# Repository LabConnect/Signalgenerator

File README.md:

LabConnect - DDS-Signalgenerator
================================

In diesem Repository werden die Schaltpläne und Layouts für den LabConnect Signalgenerator zu finden sein.

Was ist geplant?
----------------
* 1Hz bis c.a. 12.5MHz Ausgangsfrequenz in der kleinen Version
* 1Hz bis c.a. 25MHz Ausgangsfrequenz in der großen Version
* Sinus-, Dreieck- und Rechteckförmige Ausgangssignale in der kleinen Version
* Sinusförmiges Ausgangssignal in der großen Version
* Indentifikations LED
* Mikro USB Buchse
* SMA oder SMB Stecker als Signalausgang
* Bauliche Trennung von analoger und digitaler Masse

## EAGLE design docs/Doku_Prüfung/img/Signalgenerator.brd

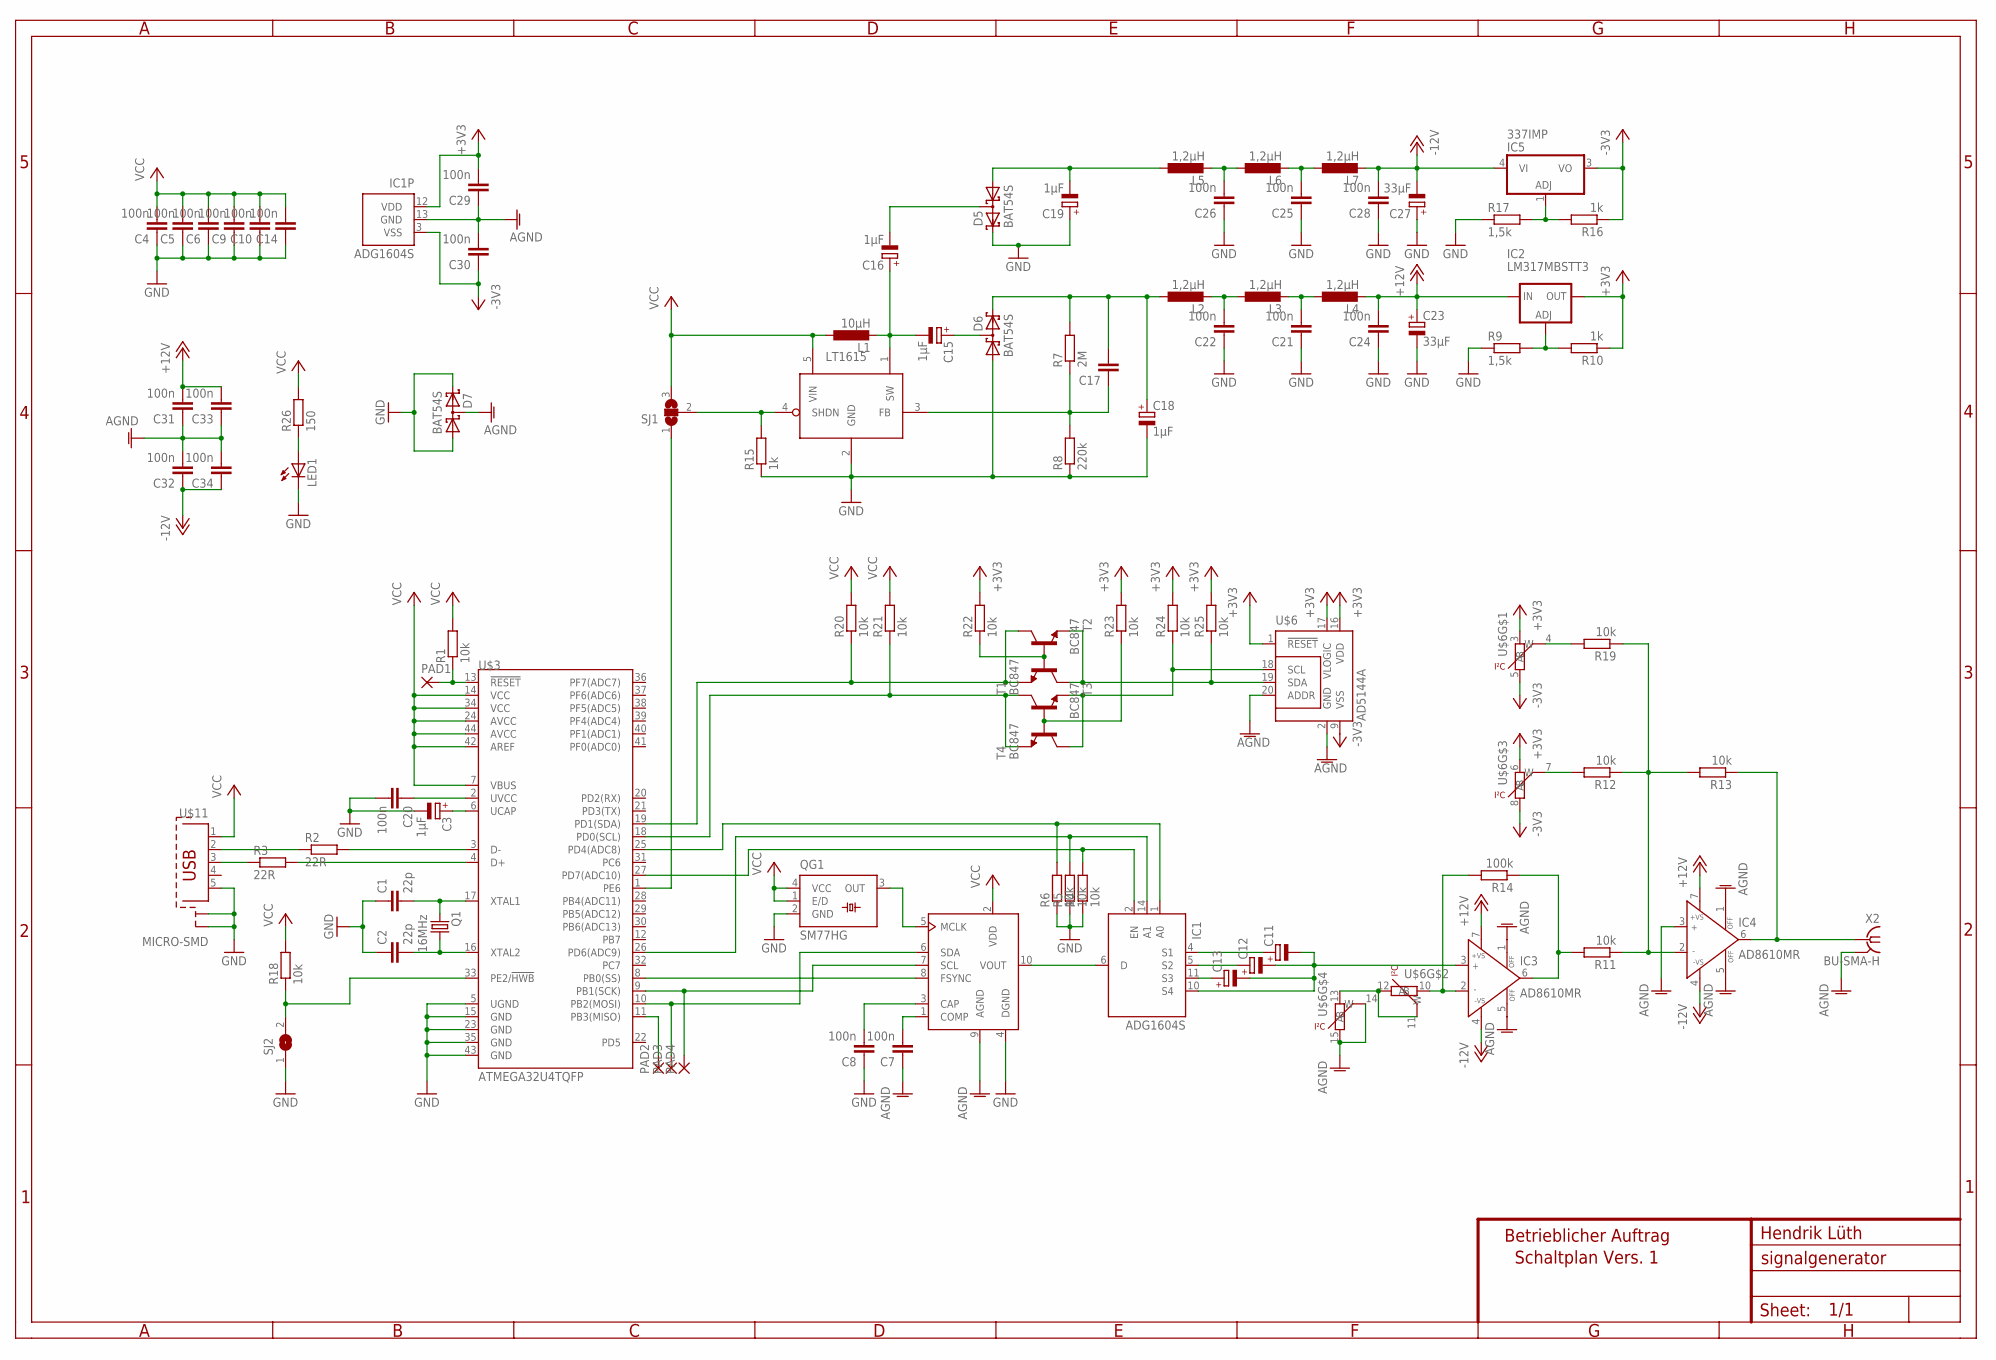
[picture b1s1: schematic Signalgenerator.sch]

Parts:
C1, C2: 22p; C0603
C3, C15, C16, C18, C19: 1µF; SMC_A
C4, C5, C6, C7, C8, C9, C10, C14, C20, C21, C22, C24, C25, C26, C28, C29, C30, C31, C32, C33, C34: 100n; C0603
C11, C12, C13: CPOL-EUSMCB; SMC_B
C17: C-EUC0603; C0603
C23, C27: 33µF; SMC_B
D5, D6, D7: BAT54S; SOT23
IC1: ADG1604S; TSSOP14
IC2: LM317MBSTT3; SOT223
IC3, IC4: AD8610MR; MSOP08
IC5: 337IMP; SOT223
L1: 10µH; L3015
L2, L3, L4, L5, L6, L7: 1,2µH; R0805
LED1: LEDCHIP-LED0603; CHIP-LED0603
PAD1, PAD2, PAD3, PAD4: WIREPADSMD1,27-254; SMD1,27-2,54
Q1: 16MHz; SM77H
QG1: SM77HG; SM77H-G
R1, R4, R5, R6, R11, R12, R13, R18, R19, R20, R21, R22, R23, R24, R25: 10k; R0603
R2, R3: 22R; R0603
R7: 2M; R0603
R8: 220k; R0603
R9, R17: 1,5k; R0603
R10, R15, R16: 1k; R0603
R14: 100k; R0603
R26: 150; R0603
SJ1: SJ2W; SJ_2
SJ2: SJ
T1, T2, T3, T4: BC847; SOT23
U$1: AD9833-SMD; MSOP10
U$2: LT1615; SOT23-5
U$3: ATMEGA32U4TQFP; SPARKFUN-DIGITALIC_TQFP44
U$6: AD5144A; TSSOP20
U$10: A3-LOC; A3L-LOC
U$11: MICRO-SMD; MIKRO
X2: BU-SMA-H

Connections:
+3V3: C29.2, IC1.12 (VDD), IC2.4 (OUT), R10.1, R22.2, R23.2, R24.2, R25.2, U$6.1 (!RESET), U$6.3 (A), U$6.6 (A), U$6.16 (VDD), U$6.17 (VLOGIC)
+12V: C23.+, C24.2, C31.2, C33.2, IC2.3 (IN), IC3.7 (+VS), IC4.7 (+VS), L4.2
-3V3: C30.1, IC1.3 (VSS), IC5.3 (VO), R16.1, U$6.5 (B), U$6.8 (B), U$6.9 (VSS)
-12V: C27.-, C28.2, C32.1, C34.1, IC3.4 (-VS), IC4.4 (-VS), IC5.4 (VI), L7.2
AGND: C7.1, C29.1, C30.2, C31.1, C32.2, C33.1, C34.2, D7.3 (C1A2), IC1.13 (GND), IC3.1 (OFF), IC3.5 (OFF), IC4.1 (OFF), IC4.3 (IN+), IC4.5 (OFF), U$1.9 (AGND), U$6.2 (GND), U$6.14 (W), U$6.15 (B), U$6.20 (ADDR), X2.2, X2.3 (2), X2.4 (2), X2.5 (2)
GND: C1.1, C2.1, C3.-, C4.1, C5.1, C6.1, C8.1, C9.1, C10.1, C14.1, C18.-, C19.+, C20.2, C21.1, C22.1, C23.-, C24.1, C25.1, C26.1, C27.+, C28.1, D5.2 (C2), D6.1 (A1), D7.1 (A1), D7.2 (C2), LED1.C, QG1.2 (GND), R4.1, R5.1, R6.1, R8.1, R9.1, R15.1, R17.1, SJ2.1, U$1.4 (DGND), U$2.2 (GND), U$3.5 (UGND), U$3.15 (GND), U$3.23 (GND), U$3.35 (GND), U$3.43 (GND), U$11.5, U$11.G1 (S1), U$11.G2 (S1), U$11.G3 (S2), U$11.G4 (S2)
unnamed: C2.2, Q1.1, U$3.16 (XTAL2)
unnamed: C1.2, Q1.3 (2), U$3.17 (XTAL1)
unnamed: C15.+, D6.3 (C1A2)
unnamed: PAD3.1, U$1.6 (SDA), U$3.10 (PB2(MOSI))
unnamed: R2.2, U$3.3 (D-)
unnamed: R3.2, U$3.4 (D+)
unnamed: R18.1, SJ2.2, U$3.33 (PE2/!HWB)
unnamed: PAD1.1, R1.1, U$3.13 (!RESET)
unnamed: PAD4.1, U$1.7 (SCL), U$3.9 (PB1(SCK))
unnamed: U$1.8 (FSYNC), U$3.8 (PB0(SS))
unnamed: C8.2, U$1.3 (CAP)
unnamed: C7.2, U$1.1 (COMP)
unnamed: R3.1, U$11.3
unnamed: R2.1, U$11.2
unnamed: QG1.3 (OUT), U$1.5 (MCLK)
unnamed: IC1.6 (D), U$1.10 (VOUT)
unnamed: C13.+, IC1.11 (S3)
unnamed: C12.+, IC1.5 (S2)
unnamed: C11.+, IC1.4 (S1)
unnamed: C11.-, C12.-, C13.-, IC1.10 (S4), IC3.3 (IN+)
unnamed: IC1.2 (EN), R4.2, U$3.27 (PD7(ADC10))
unnamed: IC1.14 (A1), R5.2, U$3.26 (PD6(ADC9))
unnamed: IC1.1 (A0), R6.2, U$3.25 (PD4(ADC8))
unnamed: C16.-, D5.3 (C1A2)
unnamed: C15.-, C16.+, L1.P$2 (2), U$2.1 (SW)
unnamed: C22.2, L2.2, L3.1
unnamed: C17.1, R7.1, R8.2, U$2.3 (FB)
unnamed: C21.2, L3.2, L4.1
unnamed: C17.2, C18.+, D6.2 (C2), L2.1, R7.2
unnamed: IC2.1 (ADJ), R9.2, R10.2
unnamed: C19.-, D5.1 (A1), L5.1
unnamed: IC4.2 (IN-), R11.1, R12.1, R13.2, R19.1
unnamed: R19.2, U$6.4 (W)
unnamed: IC3.2 (IN-), R14.2, U$6.10 (A)
unnamed: IC3.6 (OUT), R11.2, R14.1
unnamed: IC4.6 (OUT), R13.1, X2.1
unnamed: C26.2, L5.2, L6.1
unnamed: C25.2, L6.2, L7.1
unnamed: SJ1.1, U$3.1 (PE6)
unnamed: R15.2, SJ1.2, U$2.4 (SHDN)
unnamed: IC5.1 (ADJ), R16.2, R17.2
unnamed: R21.1, T3.2 (E), T4.3 (C), U$3.18 (PD0(SCL))
unnamed: R20.1, T1.3 (C), T2.2 (E), U$3.19 (PD1(SDA))
unnamed: U$6.11 (W), U$6.12 (B), U$6.13 (A)
unnamed: R12.2, U$6.7 (W)
unnamed: R22.1, T1.1 (B), T2.1 (B)
unnamed: R23.1, T3.1 (B), T4.1 (B)
unnamed: R24.1, T3.3 (C), T4.2 (E), U$6.18 (SCL)
unnamed: R25.1, T1.2 (E), T2.3 (C), U$6.19 (SDA)
unnamed: PAD2.1, U$3.11 (PB3(MISO))
unnamed: LED1.A, R26.1
unnamed: C3.+, U$3.6 (UCAP)
unnamed: C20.1, U$3.2 (UVCC)
VCC: C4.2, C5.2, C6.2, C9.2, C10.2, C14.2, L1.P$1 (1), QG1.1 (E/D), QG1.4 (VCC), R1.2, R18.2, R20.2, R21.2, R26.2, SJ1.3, U$1.2 (VDD), U$2.5 (VIN), U$3.7 (VBUS), U$3.14 (VCC), U$3.24 (AVCC), U$3.34 (VCC), U$3.42 (AREF), U$3.44 (AVCC), U$11.1

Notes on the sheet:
Hendrik Lüth
Betrieblicher Auftrag
Schaltplan Vers. 1

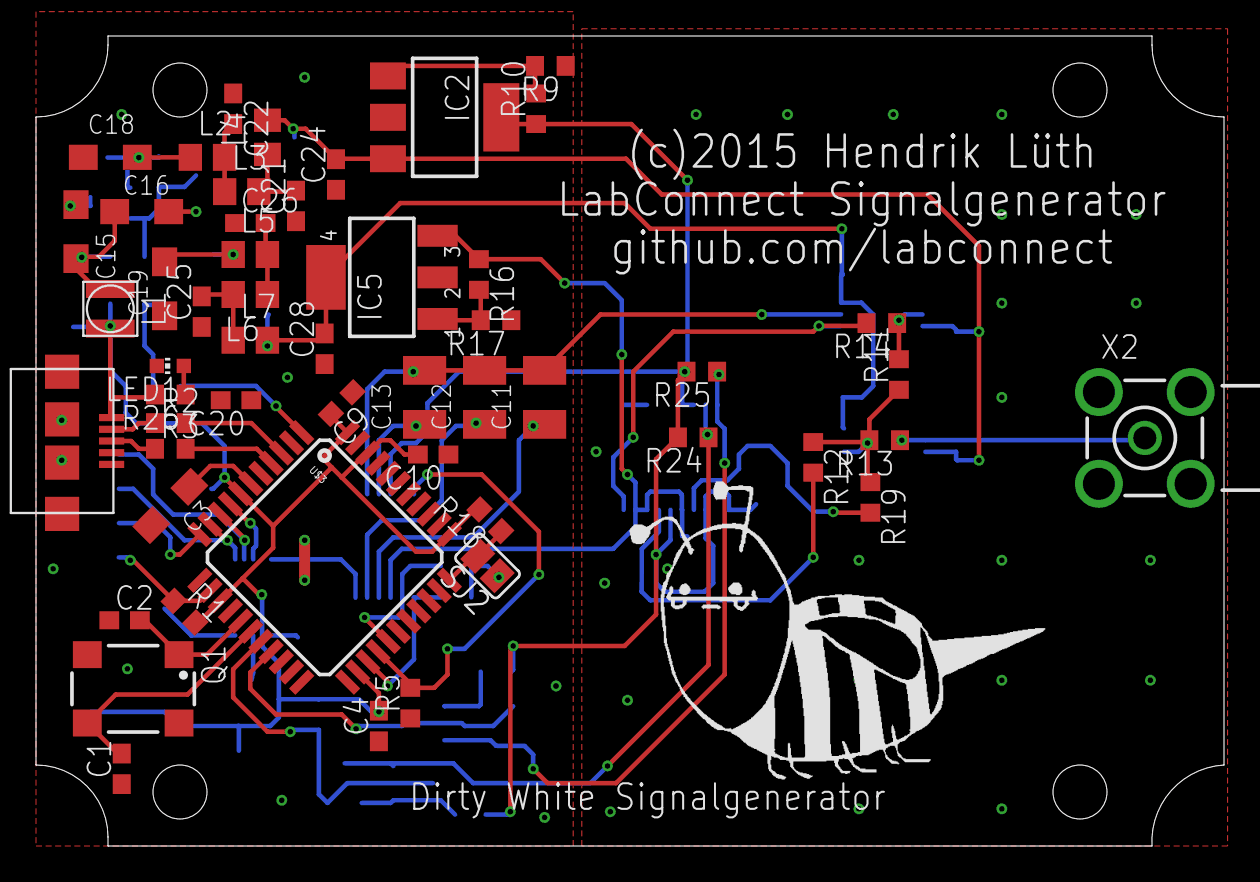
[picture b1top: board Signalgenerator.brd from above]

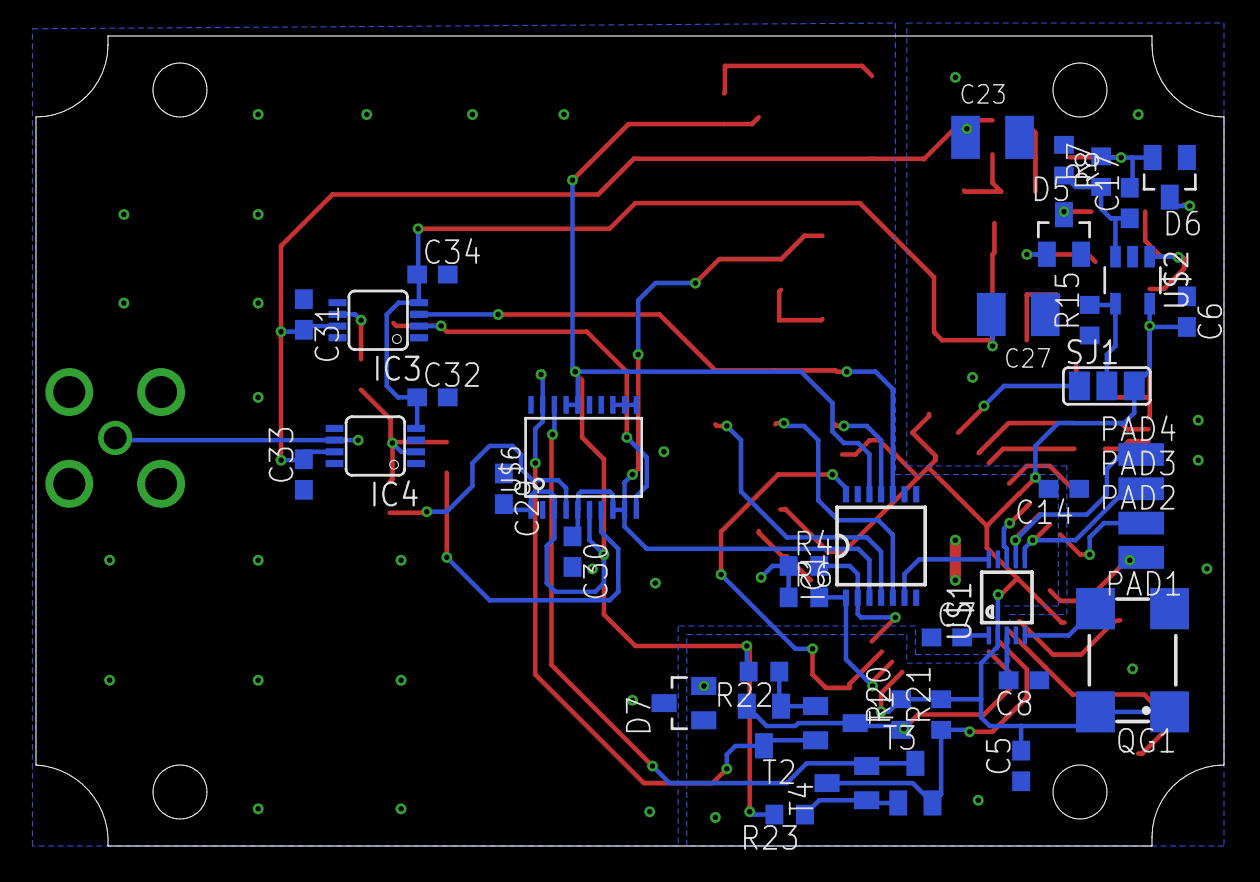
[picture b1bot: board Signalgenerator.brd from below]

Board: 2 copper layers, 66.0 x 45.0 mm, 96 parts (42 on the bottom side), 60 nets.

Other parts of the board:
U$12: BIENE

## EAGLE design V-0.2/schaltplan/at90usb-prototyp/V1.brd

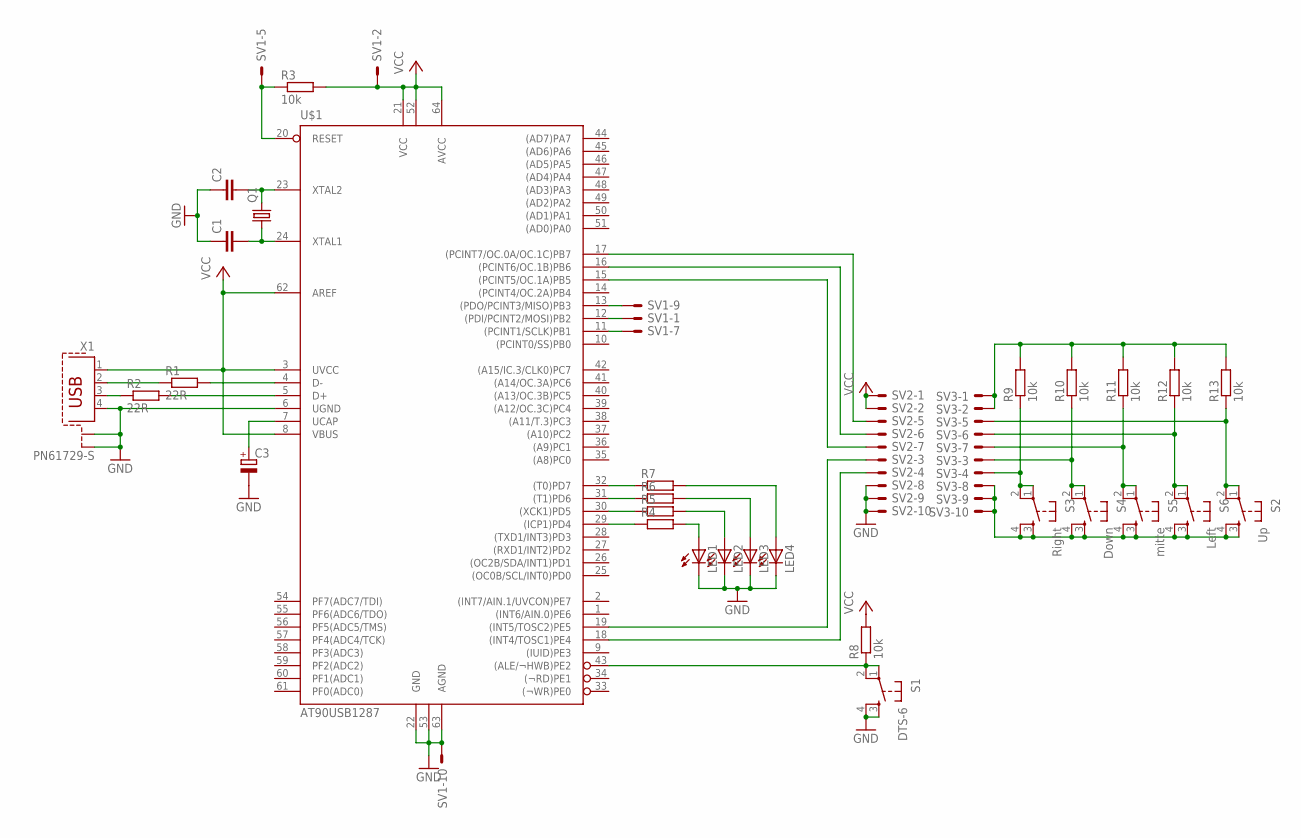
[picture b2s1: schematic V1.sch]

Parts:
C1, C2: C-EUC1206K; C1206K
C3: CPOL-EUE2-5; E2-5
LED1, LED2, LED3, LED4: LED3MM
Q1: CRYSTALSM77H; SM77H
R1, R2: 22R; M1206
R3: 10k; 0207/10
R4, R5, R6, R7: R-EU_0207/10; 0207/10
R8, R9, R10, R11, R12, R13: 10k; M1206
S1: DTS-6
S2: Up; DTS-6
S3: Right; DTS-6
S4: Down; DTS-6
S5: mitte; DTS-6
S6: Left; DTS-6
SV1, SV2, SV3: ML10E; ML10
U$1: AT90USB1287; TQFP64
X1: PN61729-S

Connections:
GND: C1.1, C2.1, C3.-, LED1.K (C), LED2.K (C), LED3.K (C), LED4.K (C), S1.3, S1.4, SV1.10, SV2.8, SV2.9, SV2.10, U$1.6 (UGND), U$1.22 (GND), U$1.53 (GND1), U$1.63 (AGND), X1.4, X1.S1, X1.S2
unnamed: R1.2, U$1.4 (D-)
unnamed: R2.2, U$1.5 (D+)
unnamed: R1.1, X1.2
unnamed: R2.1, X1.3
unnamed: C2.2, Q1.3 (2), U$1.23 (XTAL2)
unnamed: C1.2, Q1.1, U$1.24 (XTAL1)
unnamed: R4.1, U$1.29 ((ICP1)PD4)
unnamed: C3.+, U$1.7 (UCAP)
unnamed: R5.1, U$1.30 ((XCK1)PD5)
unnamed: R6.1, U$1.31 ((T1)PD6)
unnamed: R3.1, SV1.5, U$1.20 (RESET)
unnamed: SV1.9, U$1.13 ((PDO/PCINT3/MISO)PB3)
unnamed: SV1.1, U$1.12 ((PDI/PCINT2/MOSI)PB2)
unnamed: SV1.7, U$1.11 ((PCINT1/SCLK)PB1)
unnamed: R7.1, U$1.32 ((T0)PD7)
unnamed: LED1.A, R4.2
unnamed: LED2.A, R5.2
unnamed: LED3.A, R6.2
unnamed: LED4.A, R7.2
unnamed: R8.1, S1.1, S1.2, U$1.43 ((ALE/¬HWB)PE2)
unnamed: R13.1, S2.1, S2.2, SV3.5
unnamed: R12.1, S6.1, S6.2, SV3.6
unnamed: SV2.4, U$1.18 ((INT4/TOSC1)PE4)
unnamed: SV2.3, U$1.19 ((INT5/TOSC2)PE5)
unnamed: SV2.7, U$1.15 ((PCINT5/OC.1A)PB5)
unnamed: SV2.6, U$1.16 ((PCINT6/OC.1B)PB6)
unnamed: SV2.5, U$1.17 ((PCINT7/OC.0A/OC.1C)PB7)
unnamed: R11.1, S5.1, S5.2, SV3.7
unnamed: R10.1, S4.1, S4.2, SV3.3
unnamed: R9.1, S3.1, S3.2, SV3.4
unnamed: S2.3, S2.4, S3.3, S3.4, S4.3, S4.4, S5.3, S5.4, S6.3, S6.4, SV3.8, SV3.9, SV3.10
unnamed: R9.2, R10.2, R11.2, R12.2, R13.2, SV3.1, SV3.2
VCC: R3.2, R8.2, SV1.2, SV2.1, SV2.2, U$1.3 (UVCC), U$1.8 (VBUS), U$1.21 (VCC), U$1.52 (VCC1), U$1.62 (AREF), U$1.64 (AVCC), X1.1

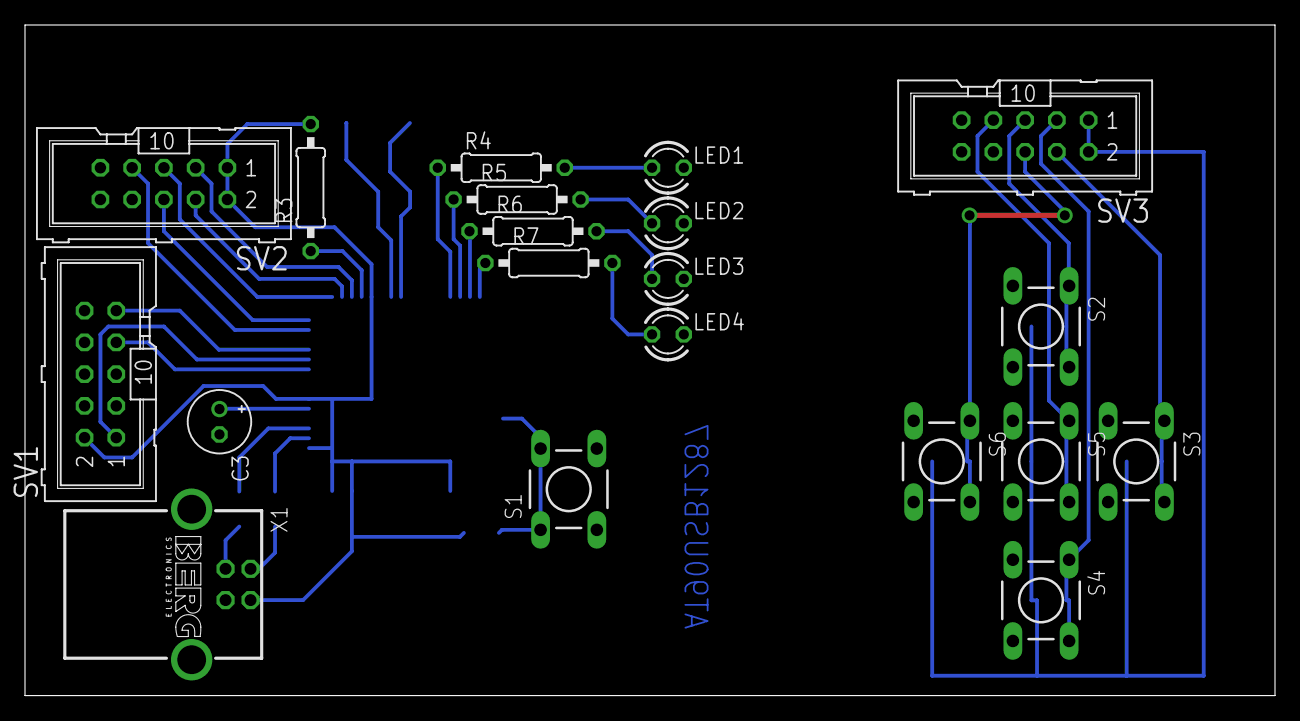
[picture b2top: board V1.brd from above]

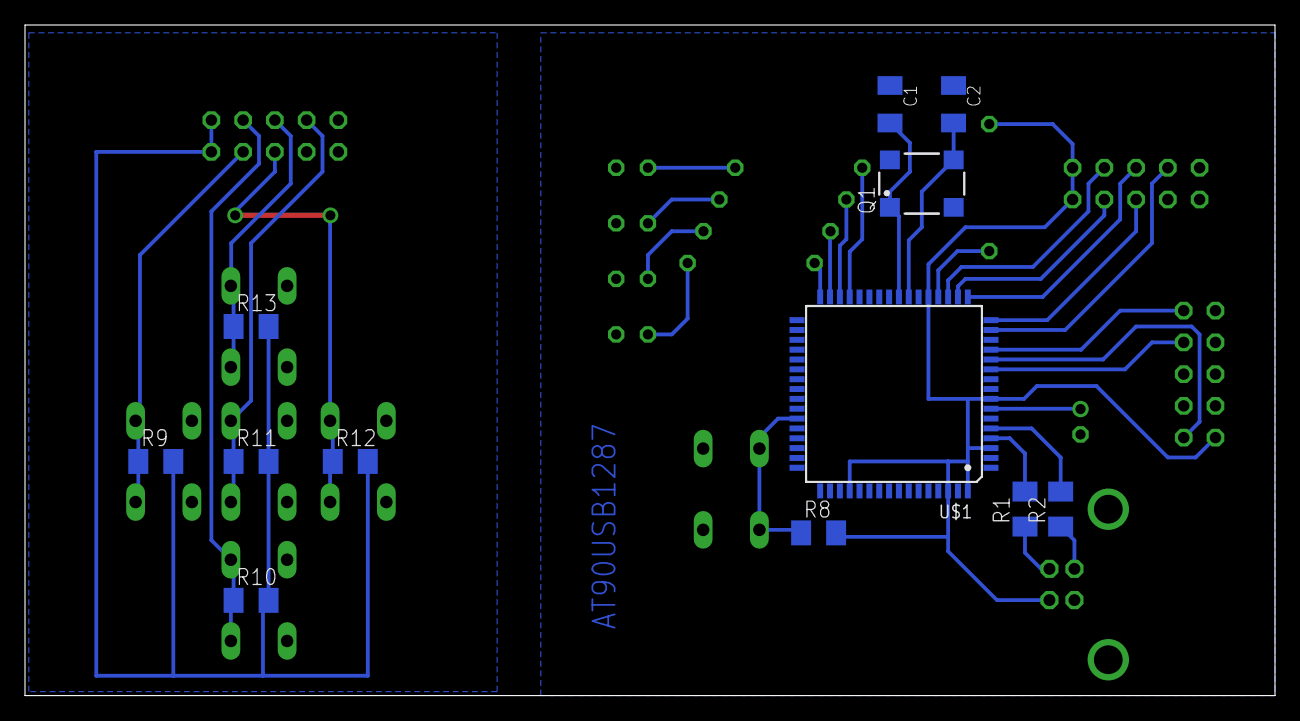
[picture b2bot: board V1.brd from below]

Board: 2 copper layers, 100.0 x 53.6 mm, 32 parts (12 on the bottom side), 34 nets.

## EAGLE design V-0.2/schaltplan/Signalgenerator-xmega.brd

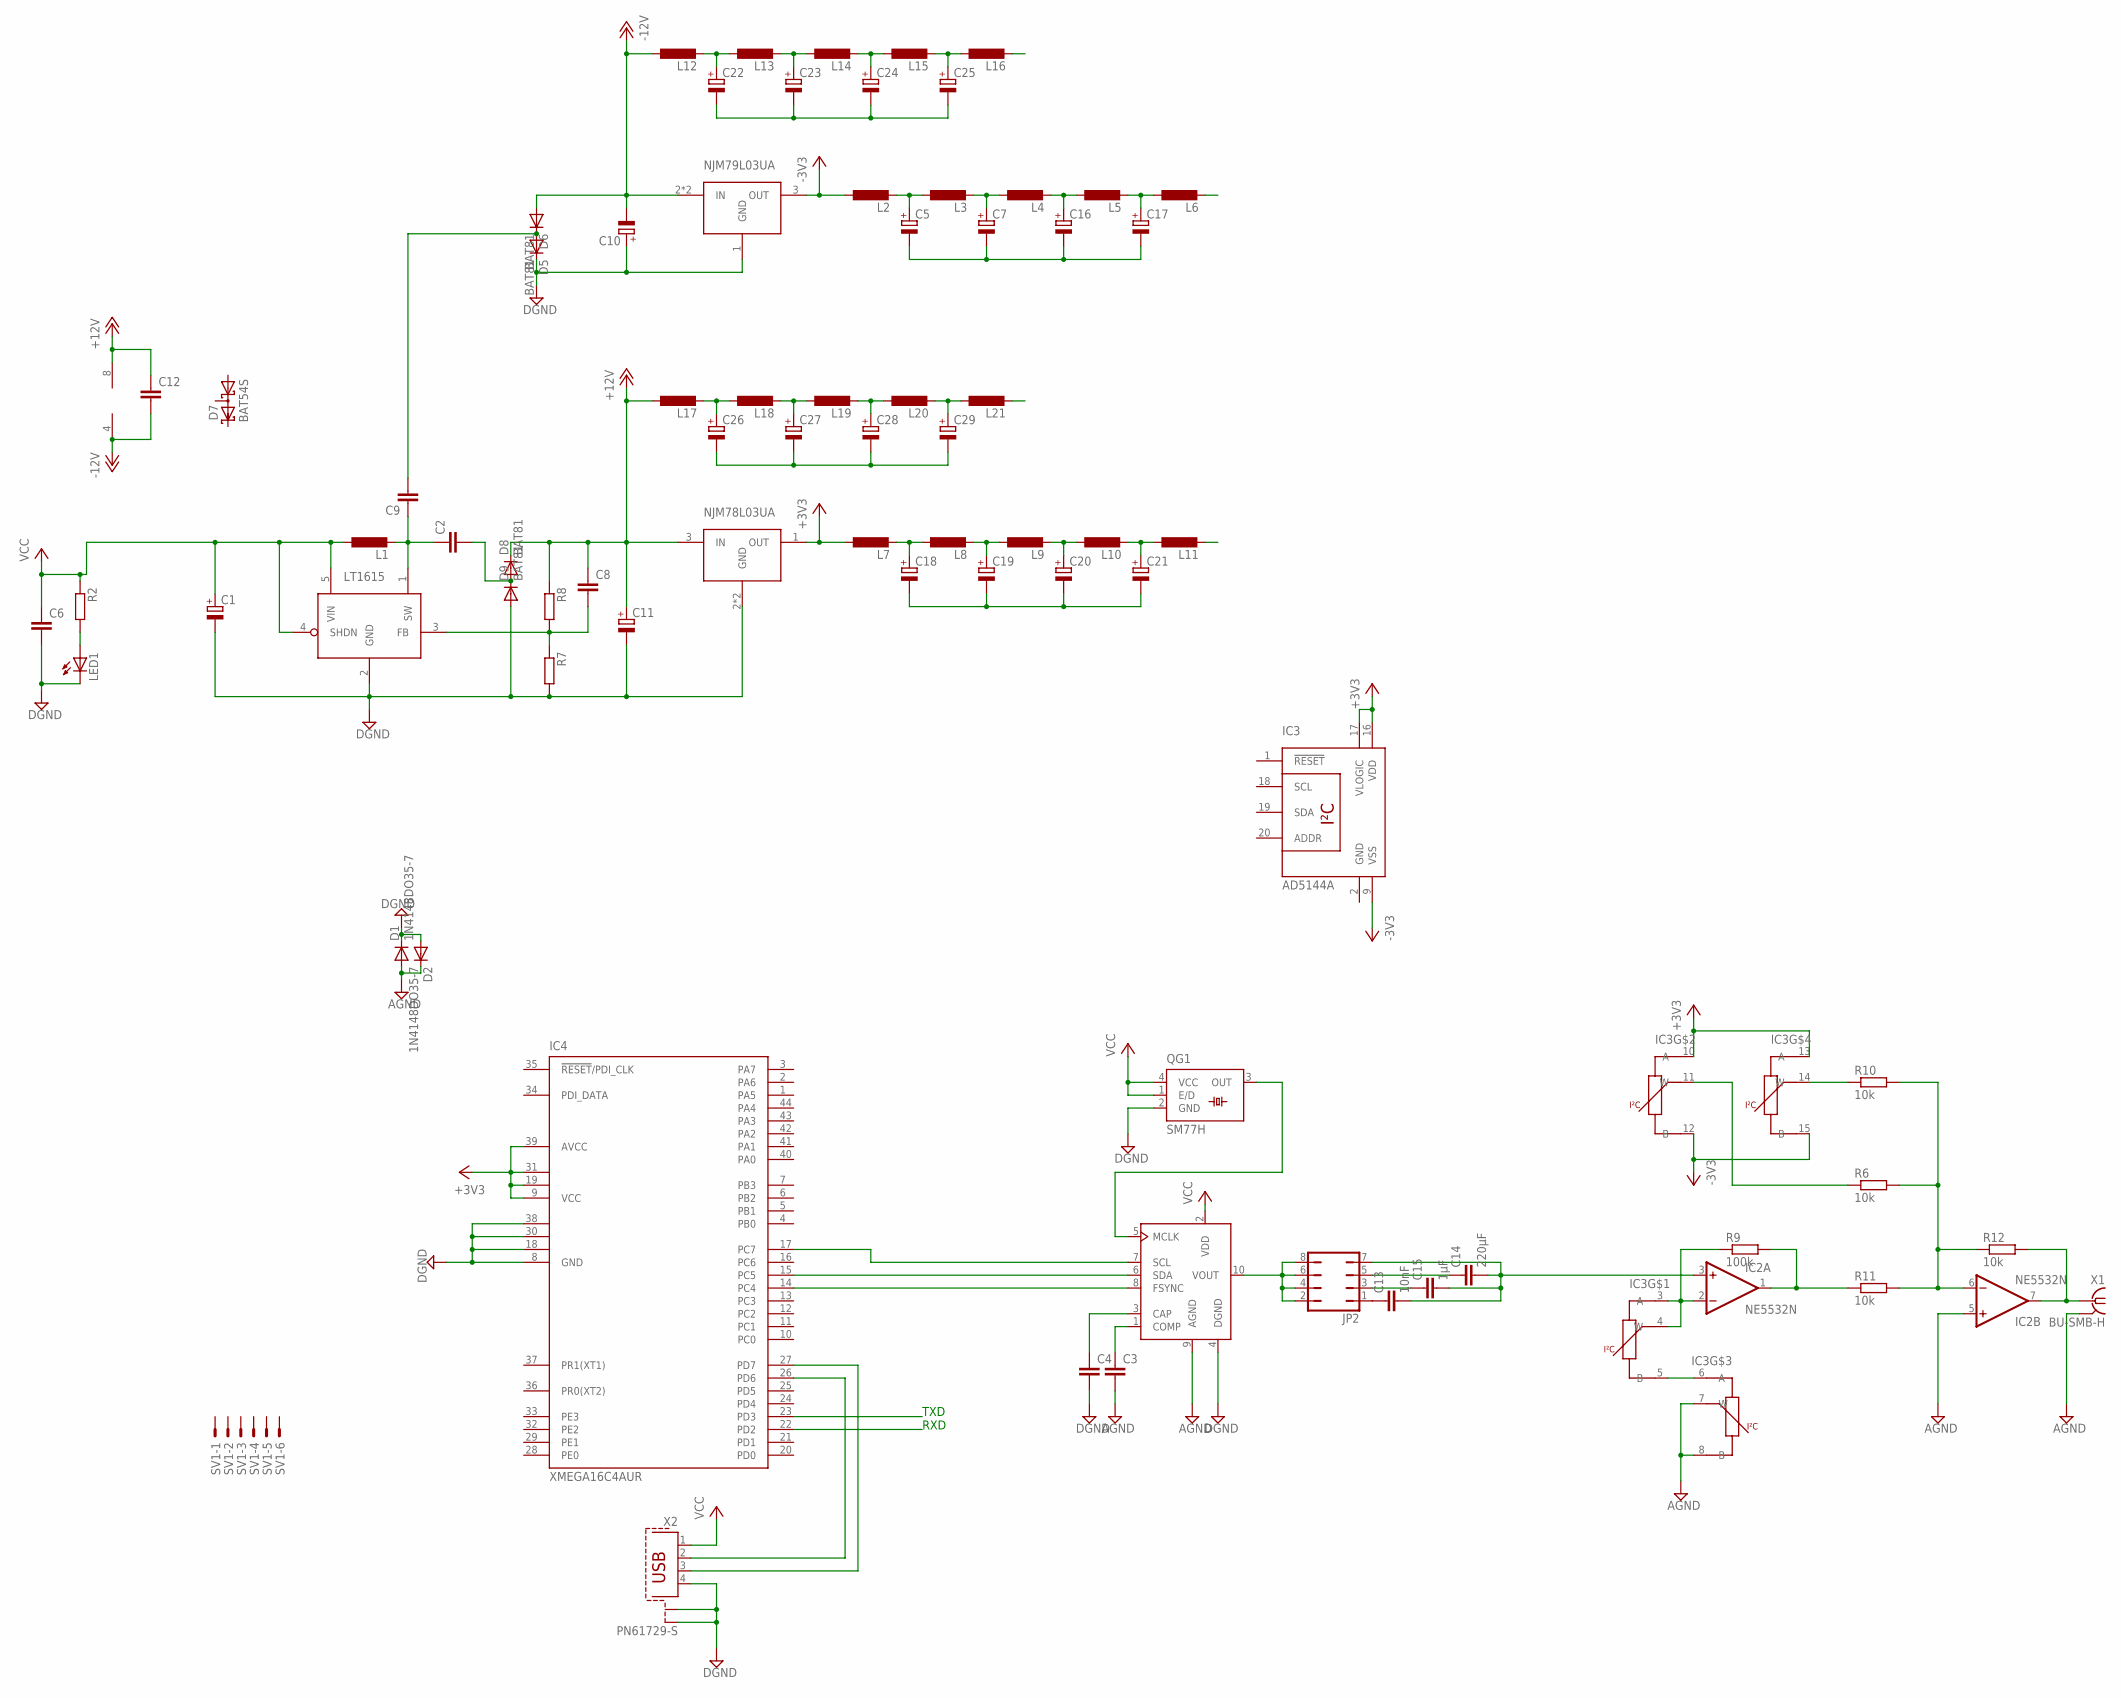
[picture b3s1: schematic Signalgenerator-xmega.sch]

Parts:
C1, C10, C11: CPOL-EUE3.5-8; E3,5-8
C2, C3, C4, C6, C8, C9, C12: C-EU025-024X044; C025-024X044
C5, C7, C16, C17, C18, C19, C20, C21, C22, C23, C24, C25, C26, C27, C28, C29: CPOL-EUE2.5-7; E2,5-7
C13: 10nF; C025-024X044
C14: 220µF; C025-024X044
C15: 1µF; C025-024X044
D1, D2: 1N4148DO35-7; DO35-7
D5, D6, D8, D9: BAT81; DO34-7
D7: BAT54S; SOT23
IC2: NE5532N; DIL08
IC3: AD5144A; TSSOP20
IC4: XMEGA16C4AUR; TQFP44
JP2: JP4Q
L1, L2, L3, L4, L5, L6, L7, L8, L9, L10, L11, L12, L13, L14, L15, L16, L17, L18, L19, L20, L21: L-EU0207/10; 0207/10
LED1: LED5MM
QG1: SM77H
R2, R7, R8: R-EU_0207/10; 0207/10
R6, R10, R11, R12: 10k; 0207/10
R9: 100k; 0207/10
SV1: ML6E; ML6
U$1: AD9833-P; DIL10
U$2: LT1615; SOT23-5
U$3: NJM79L03UA; SOT89
U$4: NJM78L03UA; SOT89
X1: BU-SMB-H
X2: PN61729-S

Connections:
+3V3: IC3.10 (A), IC3.13 (A), IC3.16 (VDD), IC3.17 (VLOGIC), IC4.9 (VCC), IC4.19 (VCC1), IC4.31 (VCC2), IC4.39 (AVCC), L7.1, U$4.1 (OUT)
+12V: C8.1, C11.+, C12.1, D8.C, IC2.8 (V+), L17.1, R8.1, U$4.3 (IN)
-3V3: IC3.9 (VSS), IC3.12 (B), IC3.15 (B), L2.1, U$3.3 (OUT)
-12V: C10.-, C12.2, D6.A, IC2.4 (V-), L12.1, U$3.2 (IN), U$3.2@1 (IN)
AGND: C3.2, D1.A, D2.C, IC2.5 (+IN), IC3.7 (W), IC3.8 (B), U$1.9 (AGND), X1.2, X1.3 (2), X1.4 (2), X1.5 (2)
DGND: C1.-, C4.2, C6.2, C10.+, C11.-, D1.C, D2.A, D5.C, D9.A, IC4.8 (GND), IC4.18 (GND1), IC4.30 (GND2), IC4.38 (GND3), LED1.K (C), QG1.2 (GND), R7.2, U$1.4 (DGND), U$2.2 (GND), U$3.1 (GND), U$4.2 (GND), U$4.2@1 (GND), X2.4, X2.S1, X2.S2
unnamed: IC4.17 (PC7), U$1.7 (SCL)
unnamed: IC4.26 (PD6), X2.2
unnamed: C3.1, U$1.1 (COMP)
unnamed: IC4.15 (PC5), U$1.6 (SDA)
unnamed: IC4.27 (PD7), X2.3
unnamed: IC4.14 (PC4), U$1.8 (FSYNC)
unnamed: C5.-, C7.-, C16.-, C17.-
unnamed: C5.+, L2.2, L3.1
unnamed: C4.1, U$1.3 (CAP)
unnamed: C7.+, L3.2, L4.1
unnamed: QG1.3 (OUT), U$1.5 (MCLK)
unnamed: C16.+, L4.2, L5.1
unnamed: C17.+, L5.2, L6.1
unnamed: LED1.A, R2.2
unnamed: C18.+, L7.2, L8.1
unnamed: C19.+, L8.2, L9.1
unnamed: C8.2, R7.1, R8.2, U$2.3 (FB)
unnamed: JP2.2, JP2.4, JP2.6, JP2.8, U$1.10 (VOUT)
unnamed: C9.2, D5.A, D6.C
unnamed: C2.1, C9.1, L1.2, U$2.1 (SW)
unnamed: C14.1, JP2.5
unnamed: C2.2, D8.A, D9.C
unnamed: C13.1, JP2.1
unnamed: IC2.2 (-IN), IC3.3 (A), IC3.4 (W), R9.1
unnamed: C13.2, C14.2, C15.2, IC2.3 (+IN), JP2.7
unnamed: IC2.1 (OUT), R9.2, R11.1
unnamed: IC2.6 (-IN), R6.2, R10.2, R11.2, R12.1
unnamed: IC2.7 (OUT), R12.2, X1.1
unnamed: C15.1, JP2.3
unnamed: IC3.5 (B), IC3.6 (A)
unnamed: IC3.14 (W), R10.1
unnamed: IC3.11 (W), R6.1
unnamed: C20.+, L9.2, L10.1
unnamed: C21.+, L10.2, L11.1
unnamed: C18.-, C19.-, C20.-, C21.-
unnamed: C22.+, L12.2, L13.1
unnamed: C23.+, L13.2, L14.1
unnamed: C24.+, L14.2, L15.1
unnamed: C25.+, L15.2, L16.1
unnamed: C22.-, C23.-, C24.-, C25.-
unnamed: C26.+, L17.2, L18.1
unnamed: C27.+, L18.2, L19.1
unnamed: C28.+, L19.2, L20.1
unnamed: C29.+, L20.2, L21.1
unnamed: C26.-, C27.-, C28.-, C29.-
VCC: C1.+, C6.1, L1.1, QG1.1 (E/D), QG1.4 (VCC), R2.1, U$1.2 (VDD), U$2.4 (SHDN), U$2.5 (VIN), X2.1

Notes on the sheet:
TXD RXD

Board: 2 copper layers, 78 parts (6 on the bottom side), 52 nets, no tracks yet.

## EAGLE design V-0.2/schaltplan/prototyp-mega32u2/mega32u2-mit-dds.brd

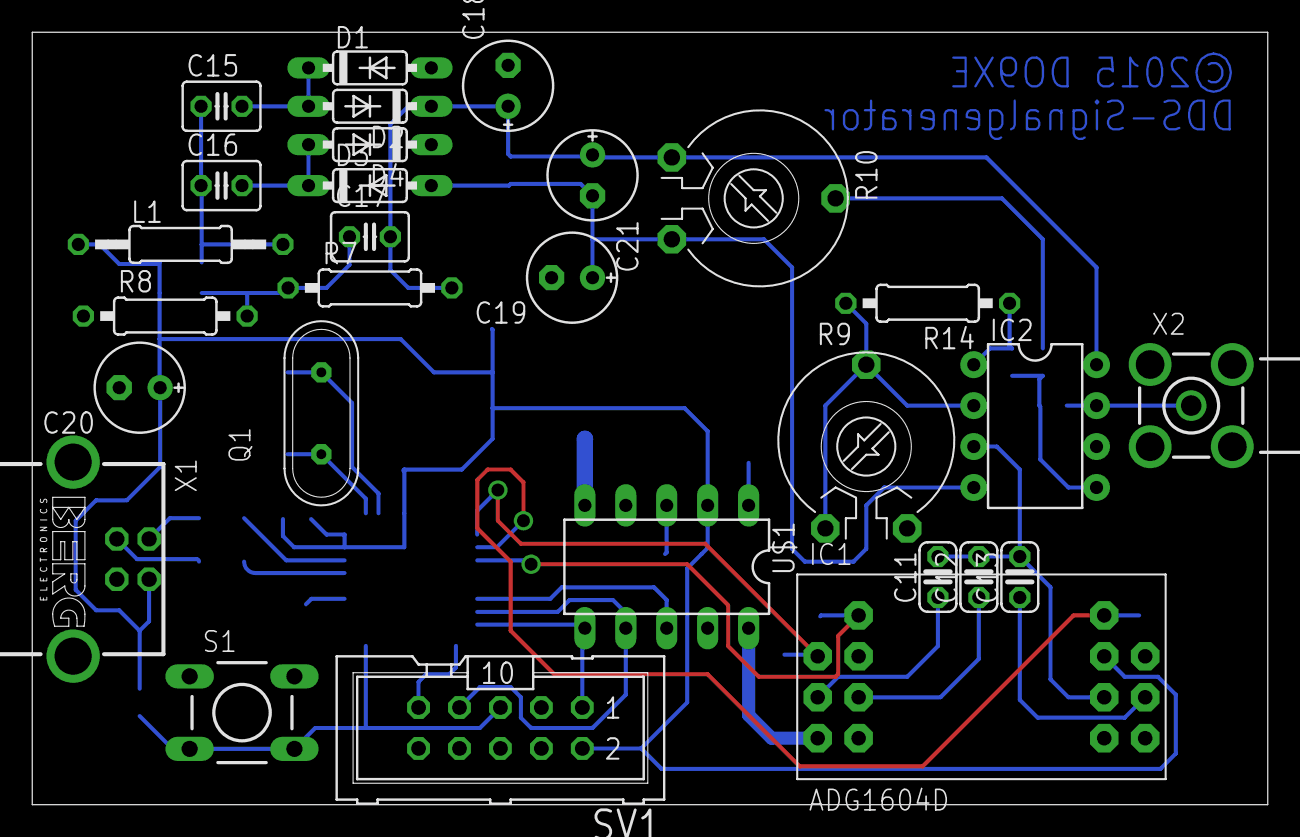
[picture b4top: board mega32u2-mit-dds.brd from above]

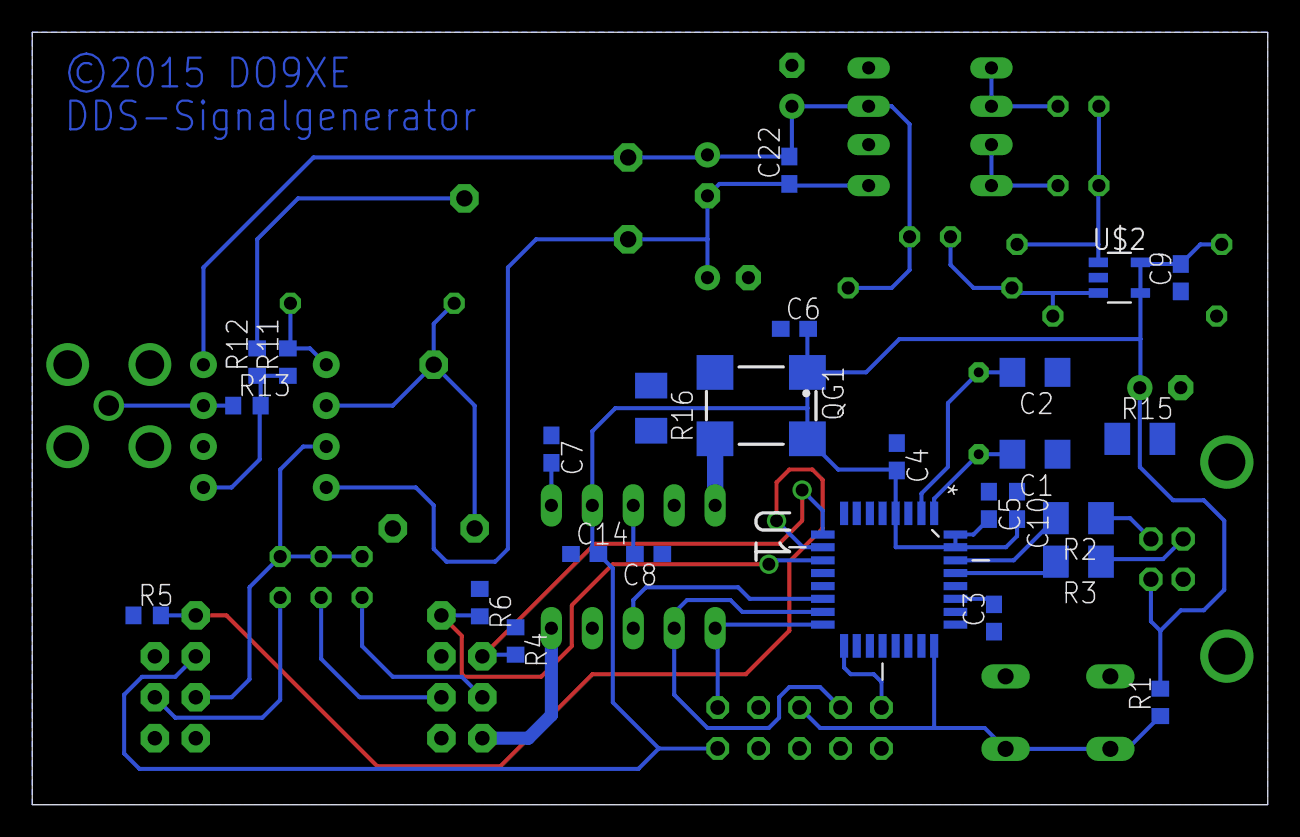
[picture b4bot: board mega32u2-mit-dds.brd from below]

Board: 2 copper layers, 76.7 x 47.9 mm, 54 parts (26 on the bottom side), 36 nets.

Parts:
C1, C2: 22n; C1206
C3, C4, C5, C6, C7, C8, C9, C10, C14, C22: 100n; C0603
C11, C12, C13: C025-024X044
C15, C16, C17: C025-030X050
C18, C19, C20, C21: E2,5-6E
D1, D2, D3, D4: DO35-7
IC1: ADG1604D; DIL2-14
IC2: NE5532N; DIL08
L1: 0207/12
Q1: QS
QG1: SM77HG; SM77H-G
R1, R4, R5, R6, R11, R12, R13: 10k; R0603
R2, R3: 22R; M1206
R7: 2M; 0207/10
R8: 220k; 0207/10
R9: 100k; PT-10
R10: PT-10
R14: 100k; 0207/10
R15: M1206
R16: 0; M1206
S1: DTS-6
SV1: ML10
U1: ATMEGA32U2-AU; QFP80P900X900X120-32N
U$1: AD9833-P; DIL10
U$2: LT1615; SOT23-5
X1: PN61729-S
X2: BU-SMA-H

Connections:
GND: C1.1, C2.1, C3.1, C4.1, C5.1, C6.1, C7.1, C8.1, C9.1, C10.1, C14.1, C18.-, C19.-, C20.-, D1.A, D4.C, IC1.P$3, IC1.P$13, IC2.6, QG1.2, R4.1, R5.1, R6.1, R8.1, R9.2, R15.1, R15.2, R16.1, R16.2, S1.1, S1.2, SV1.10, U1.3, U1.28, U$1.4, U$1.9, U$2.2, X1.4, X1.S1, X1.S2, X2.2, X2.3, X2.4, X2.5
unnamed: C2.2, Q1.2, U1.2
unnamed: C1.2, Q1.1, U1.1
unnamed: SV1.9, U1.17
unnamed: SV1.1, U1.16, U$1.6
unnamed: R2.2, U1.30
unnamed: R3.2, U1.29
unnamed: C3.2, U1.27
unnamed: R1.1, S1.3, S1.4, SV1.5, U1.24
unnamed: SV1.7, U1.15, U$1.7
unnamed: U1.14, U$1.8
unnamed: C8.2, U$1.3
unnamed: C7.2, U$1.1
unnamed: R3.1, X1.3
unnamed: R2.1, X1.2
unnamed: QG1.3, U$1.5
unnamed: IC1.P$6, U$1.10
unnamed: C13.1, IC1.P$11
unnamed: C12.1, IC1.P$5
unnamed: C11.1, IC1.P$4
unnamed: C11.2, C12.2, C13.2, IC1.P$10, IC2.3
unnamed: IC1.P$2, R4.2, U1.9
unnamed: IC1.P$14, R5.2, U1.10
unnamed: IC1.P$1, R6.2, U1.11
unnamed: C15.2, D1.C, D2.A
unnamed: C15.1, C16.1, L1.2, U$2.1
unnamed: C16.2, D3.C, D4.A
unnamed: C17.1, R7.1, R8.2, U$2.3
unnamed: C17.2, C18.+, C21.+, C22.2, D2.C, IC2.8, R7.2, R10.1
unnamed: C19.+, C21.-, C22.1, D3.A, IC2.4, R10.2
unnamed: IC2.5, R11.1, R12.1, R13.2
unnamed: R10.3, R12.2
unnamed: IC2.2, R9.1, R9.3, R14.2
unnamed: IC2.1, R11.2, R14.1
unnamed: IC2.7, R13.1, X2.1
VCC: C4.2, C5.2, C6.2, C9.2, C10.2, C14.2, C20.+, IC1.P$12, L1.1, QG1.1, QG1.4, R1.2, SV1.2, U1.4, U1.31, U1.32, U$1.2, U$2.4, U$2.5, X1.1

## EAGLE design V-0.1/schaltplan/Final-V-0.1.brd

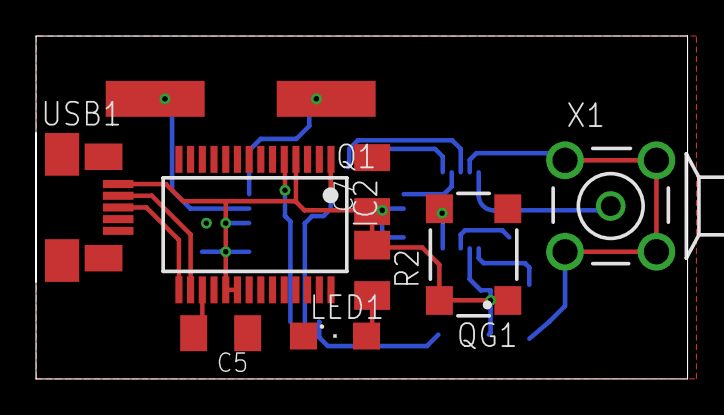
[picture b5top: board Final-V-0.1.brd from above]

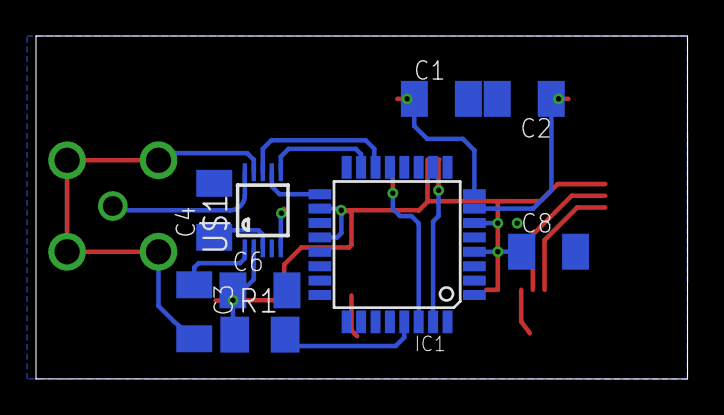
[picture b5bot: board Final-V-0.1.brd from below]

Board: 2 copper layers, 36.2 x 19.1 mm, 18 parts (9 on the bottom side), 19 nets.

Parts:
C1, C2, C3, C4, C5, C6, C7, C8: C1206K
IC1: MEGA8-AI; TQFP32-08
IC2: FT232RL; SSOP28
LED1: SML1206
Q1: CSM-7X-DU
QG1: SM77H
R1, R2: M1206
U$1: AD9833-SMD; MSOP10
USB1: MOLEX-47346-0001; MOLEX-47364-0001
X1: BU-SMB-H

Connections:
AGND: C3.2, U$1.9, X1.2, X1.3, X1.4, X1.5
DGND: C1.2, C2.2, C4.2, C5.1, C6.2, C7.2, C8.2, IC1.3, IC1.5, IC1.21, IC2.7, IC2.18, IC2.21, IC2.25, IC2.26, LED1.C, QG1.2, U$1.4, USB1.5, USB1.GND1, USB1.GND2, USB1.GND3, USB1.GND4
unnamed: C2.1, IC1.7, Q1.2
unnamed: C1.1, IC1.8, Q1.1
unnamed: C3.1, U$1.1
unnamed: IC1.17, U$1.7
unnamed: IC1.29, R1.2
unnamed: IC1.15, U$1.6
unnamed: IC1.14, U$1.8
unnamed: C4.1, U$1.3
unnamed: C5.2, IC2.17
unnamed: QG1.3, U$1.5
unnamed: U$1.10, X1.1
unnamed: IC1.30, IC2.1
unnamed: IC1.31, IC2.5
unnamed: IC2.16, USB1.2
unnamed: IC2.15, USB1.3
unnamed: LED1.A, R2.2
VCC: C6.1, C7.1, C8.1, IC1.4, IC1.6, IC1.18, IC1.20, IC2.4, IC2.19, IC2.20, QG1.1, QG1.4, R1.1, R2.1, U$1.2, USB1.1

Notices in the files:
V-0.2/schaltplan/prototyp-mega32u2/mega32u2-mit-dds.brd:
©2015 DO9XE
docs/Doku_Prüfung/img/Signalgenerator.brd:
(c)2015 Hendrik Lüth
parts and their libraries:
SparkFun-DigitalIC: Licensing: Creative Commons ShareAlike 4.0 International - https://creativecommons.org/licenses/by-sa/4.0
